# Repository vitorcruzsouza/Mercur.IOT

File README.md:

EN-US: This content was written in both English and Portuguese. To access content in English, [clique here](#enus)

PT-BR: Este conteúdo foi escrito em Inglês e em Português. Para acessar o conteúdo em Português, [clique aqui](#ptbr)

---

# EN/US
# MercurIOT - Sensor Data Transmitter via GSM
readme v1.6

## Contents

<!-- toc -->

- [1. Description](#description)
  - [Objective](#objective)
  - [Behind the name](#behind-the-name)
- [2. Plataform](#platform)
  - [Conceptualization - Electronics](#conceptualization---electronics)
  - [Conceptualization - Code](#conceptualization---code)
  - [Technical Specifications](#technical-specifications)
  - [Bill of Materials](#bill-of-materials)
- [3. Circuit Schematic](#circuit-schematic)
  - [Full System](#full-system)
  - [Power Supply](#power-supply-and-battery-charging)
  - [Microcontroller](#microcontroller)
  - [GSM Communication](#gsm-communication)
  - [Sensor 16-bit ADC](#sensor-16bit-adc)
- [4. Printed Circuit Board (PCB)](#printed-circuit-board-pcb)
  - [2D Visualization of All Layers](#2d-visualization-of-all-layers)
  - [2D Visualization of Top Layer](#2d-visualization-of-top-layer)
  - [2D Visualization of Bottom Layer](#2d-visualization-of-bottom-layer)
- [5. 3D Render of the PCB](#3d-render-of-the-pcb)
  - [Top View](#top-view)
  - [Bottom View](#bottom-view)
  - [Isometric View](#isometric-view)

- [About me](#about-me)

<!-- tocstop -->

## Description

#### Objective
Fully developing a wireless data transmission solution for industrial applications, capable of sending 500kB of sensing data remotely to be used in machine operation conditions monitoring.

The scope of this project encopasses the development of both the PCB and firmware required for operation of the microcontrollers utilized.

#### Behind the name
Inspired by the greek god Mercury, son of Zeus and messenger of the gods, MercurIOT was developed with the purpose of delivering a flexible platform, upon which multiple IOT communication solutions can be created.

## Platform 

### Conceptualization - Electronics:

To send sensor information to a distant receiver, the **GSM tecnology** was selected - the same used for 3G/4G mobile data plans - due to the ease of access to nacional brazillian infrastructure to mobile network systems (where this project was conceived), thus high capacity for long distance tranmissions.

Therefore, the **SIM7600EH** GSM communication chip was chosen, since it presents an easy to use yet powerful list of commands, high market availability and broad documentation.

For controlling the whole system and being responsible for converting the sensor data into commands the SIM7600 can understand, the Atmel **ATMEGA8U2-MU** was selected as a suitable microcontroller. Aside from having very broad documentation and market availability for being one the chips used by Arduino boards, the ATMEGA8 is specially handy for having integrated USB communication, simplifying the final board layout. Its 16MHz clock shall be sufficient to execute all of the communication with no major delays.

One of the limitations of the ATMEGA8, however, is the relatively low resolution of its ADC (Analog to Digital Converter chip), which has a 10 bit resolution (maximum of 1024 individual values in any readings). Therefore, an accompanying **ADS1115** chip was selected to improve the data quality the MercurIOT board can supply. This IC has a 16 bit resolution (max. 65,536 values) for analog readings, it can communicate in I2C protocol with other chips in its network, and can support up to 4 individual analog inputs. For this project, however, we're only going to use one.

Finally, to power the whole system, a **18650 Lithium-Ion** cell was selected, since this type of battery chemistry is very common and is currently one of the best options on Power Density to Price and/or size. Utilizing Li-Ion cells in this project allows it to be recharged, but adds a degree of complexity by requiring some battery monitoring and protection features. For this, the **BQ29707DSET** battery management IC is being used (features include overcharge protection, overdischarge protection, overcurrent protection) in conjunction with the **MT3608** boost-converter for stabilizing a 5VDC supply rail to all other electronics.

### Conceptualization - Code:

To construct a wireless transmission solution, there are a few major things that have to be considered. The first is what information is going to be sent, the second is how it is going to be sent, and third but not least how it is going to be interpreted by what's receiving it.

This way, the first problem that need to be tackled is the **information source** itself. In this project, for demonstration purposes, a hypothetical, unspecified, pre-amplified analog sensor is going to be used, as this is encopasses almost any type of application that telemetry sensors can be used in, since most physical quantity sensing devices output analog (voltage or current) signals.

Since a 16-bit capabe Analog to Digital Converter (ADC) is being used to capture these sensed signals, these 16-bit values have to be processed accordingly. For that, the Adafruit_ADS1015.h library is used, to facilitate I2C communication between the microcontroller and the ADC unit and to interpret the information.

Assuming a server is going to receive sensed data and utilize it, this processed information need to be sent via some medium. For this, the SIM7600EH chip has a list of GSM commands to perform varying tasks. If sent from the microcontroller to the GSM IC via serial UART communication, these commands will each perform an action through the 3G/4G communication line. [Here's a full list of AT commands and instructions on how to use them here.](https://usermanual.wiki/Document/SIM7500SIM760020SeriesAT20Command20ManualV107.443047306/html)

The information that is going to be transmitted, however, needs to be encoded in a certain protocol, so that both parties of this system - client (transmitter) and server (receiver) - can understand what is being relayed; and more critically, know what to do with each information given.

For this, the MQTT (Message Queuing Telemetry Transport) is used. It is a protocol based on TCP/IP network communication that simplifies parallel data transmission between multiple parties, specially for IoT applications such as this one, while providing a light and simple framework for less powerful devices to run on. [Read this for more information on how the MQTT protocol works.](https://randomnerdtutorials.com/what-is-mqtt-and-how-it-works/)

Joining the AT (GSM) and MQTT communication formats, we can compile the data collected by whichever sensor is plugged into the MercurIOT transmitter, and send it to a MQTT topic dedicated to captured sensor data, which then can be subscribed to by any software or BI (Business Inteligence) suite that whishes to utilize or display that information.

### Technical Specifications

#### Electronics

##### Control
- Microcontrolador: ATmega8U2-MU
- IC USB Communication: ATmega8U2-MU
- IC GSM Communication: SIM7600E-H
##### Power supply
- IC Battery Management: BQ29707DSET
- IC Voltage Regulator: MT3608
- Battery: Li-Ion 18650 cell
##### Sensing
- IC 16-bits Analog-Digital Converter: ADS1115

#### Code
- Library Adafruit_ADS1015.h (for I2C communication with the 16bit ADC)
- Library SoftwareSerial.h (for serial UART communication with the GSM and MQTT)
- Libraries Arduino.h, Wire.h e ArduinoLowPower.h (for using the native Arduino platform functionalities)
##### Software
- Development Environment: VSCode
- Platform: Plaform.io

### Bill of Materials

[Link to the Bill of Materials file, complete with links for ordering the parts used globally.](https://github.com/vitorcruzsouza/Mercur.IOT_TRACTIAN/blob/main/docs/BOM.md)

## Circuit Schematic
[Link to folder with circuit and PCB ECAD files.](https://github.com/vitorcruzsouza/Mercur.IOT_TRACTIAN/tree/main/hardware_sch/Mercurio_wirelessTransmitter)

### Full System
[Link to the full schematic file.](https://github.com/vitorcruzsouza/Mercur.IOT_TRACTIAN/blob/main/docs/Mercurio_SCHEMATIC-SHEET.pdf)

### Power Supply and Battery Charging

The circuit above utilizes a BQ2970 battery management IC to monitor the lithium-ion battery's voltage and offer multiple protections. By utilizing a selection of multiple internal comparators, the IC monitors the voltage coming from the positive side of the battery through the "BAT" pin 5. Either when the voltage is too high (±4.2V), too low (±3.4V) or the current is too high (overcurrent or short-circuit), the IC deactivates of its "COUT" or "DOUT" outputs to disconnect the battery's negative side to Ground, through its two CSD16301Q2 MOSFET switches.

Through the use of the MT3608 boost converter IC, both the battery's and the USB port's voltage are steped-up and regulated to 5VDC, for supplying both the ATMEGA and the SIM7600 chips. By using a zener diode between the USB port and the battery, as well as one between the boost converter an all of the componentes supplied, the circuit can be both powered on by the USB port and charge the battery simultaneously without causing a power loop.

### Microcontroller

Together with the microcontroller are a couple of passive components to allow its basic functioning, like a 16MHz clock crystal and accompanying oscillating capacitors, varistors for USB power protection and a ferrite bead for filtering, a 500mA fuse between the power circuit and the VCC port of the ATMEGA chip, a RESET button and 6 open pins (ICSP) for connecting configuration signals, such as boot loading and resetting once again.

### GSM Communication

In this schematic, two S8050 transistors can be observed in series with the TXD and RXD transmission lines that are used to connect the SIM7600E-H and the ATMEGA8U-MU via UART. This is used to decouple both chips while no data is being transmitted, since the very TXD and RXD lines activate the transistors that let the data bits pass, so that these wires do not act as antennas and pickup any interference, stopping any of the two ICs accidentally interpret noise as information.

Pins 17 - 20 are connected to the SIM card slot and therefore the SIM card inserted, and pin 82 is connected to a SMA antenna connector, so that any type or size of antenna desired can be used.

The "PWRKEY" and "RESET" are pulled to ground so that the IC is always active. One improvement this circuit design could benefit from is having the microcontroller, via a switching device, have the option to activate or deactivate both the Reset and Power-Key pins so that the IC can be rebooted or turned off completely for power saving measures.

### Sensor 16bit ADC

Last but not least, the ADS1115 16-bit ADC is connected to the SCL and SCA pins of the ATMEGA microcontroller, through which the ADC relays the sensed analog  signals through I2C serial communication. The sensor, whichever one may be chosen for the application, can be connected to the J4 screw terminal following the "VCC, Signal, GND" pinout standard.

## Printed Circuit Board (PCB)

### 2D Visualization of All Layers

For information all data lines excluding the antenna line, the traces were set to 10 mils (0.254 mm). For all other lines (power lines and antenna), the traces were set to 20 mils (0.5 mm), so that a maximum of 1.5 A can be supplied to all components and used for more power-intensive LTE data transmission.

### 2D Visualization of Top Layer

### 2D Visualization of Bottom Layer

## 3D Render of the PCB

### Top View

### Bottom View

### Isometric View

## About me

### Contact info:
<p>Vitor Cruz Souza<br>
São Paulo, SP, Brazil<br>
E-mail: vitor.cruz.souza.2001@gmail.com</p>

---

[Back to the top.](#contents)

---

# PT/BR
# MercurIOT - Transmissor de Dados de Sensor via GSM
readme v1.52

(Esta sessão ainda não foi totalmente traduzida).

## Conteúdos

<!-- toc -->

- [1. Descrição](#descrição)
  - [Objetivo](#objetivo)
  - [Por trás do nome](#por-trás-do-nome)
- [2. Plataforma](#plataforma)
  - [Conceitualização](#conceitualização)
  - [Especificações Técnicas](#especificações-técnicas)
  - [Lista de Materiais](#lista-de-materiais)
- [3. Esquemático do Circuito](#esquemático-do-circuito)
  - [Sistema Completo](#sistema-completo)
  - [Alimentação e Bateria](#alimentação-e-bateria)
  - [Microcontrolador](#microcontrolador)
  - [Comunicação GSM](#comunicação-gsm)
  - [ADC 16bits do Sensor](#adc-16bits-do-sensor)
- [4. Placa de Circuito Impresso (PCI)](#placa-de-circuito-impresso-pci)
  - [Visualização 2D de Todas as Camadas](#visualização-2d-de-todas-as-camadas)
  - [Visualização 2D da Camada Superior](#visualização-2d-da-camada-superior)
  - [Visualização 2D da Camada Inferior](#visualização-2d-da-camada-inferior)
- [5. Renderização 3D da PCI](#renderização-3d-da-pci)
  - [Vista Superior](#vista-superior)
  - [Vista Inferior](#vista-inferior)
  - [Vista Isométrica](#vista-isométrica)

- [Sobre mim](#sobre-mim)

<!-- tocstop -->

## Descrição

#### Objetivo
O objetivo do projeto MercurIOT é desenvolver uma solução completa de transmissão de dados para aplicações industriais, capaz de enviar 500kB de dados de sensoriamento remotamente, a serem usados no monitoramento de condições de operação de máquinas.

O escopo deste projeto abriga o desenvolvimento de ambos PCI e firmware necessário para operação dos microcontroladores utilizados.

#### Por trás do nome
Inspirado no deus greco-romano Mercúrio, filho de Zeus e mensageiro dos deuses, o MercurIOT foi desenvolvido com o propósito de entregar uma plataforma flexível, sobre a qual múltiplas soluções de comunicação IOT possam ser criadas.

## Plataforma

### Conceitualização

Para realizar o envio de informações do sensor à distância, foi escolhido utilizar de tecnologia GSM, a mesma utilizada para comunicação 3G/4G em telefonia móvel, devido ao fácil acesso à infraestrutura nacional brasileira de redes móveis (onde este projeto foi concebido) e, portanto, alta capacidade de transmissão de dados à longas distâncias.

### Especificações Técnicas

#### Eletrônica

##### Controle
- Microcontrolador: ATmega8U2-MU
- CI Comunicação USB: ATmega8U2-MU
- CI Comunicação GSM: SIM7600E-H
##### Alimentação
- CI Gerenciamento de Baterias: BQ29707DSET
- CI Regulador de Tensão: MT3608
- Bateria: Li-Ion 18650
##### Sensoriamento
- CI Conversor Analógico Digital 16-bits: ADS1115

#### Código
- Biblioteca Adafruit_ADS1015.h (para comunicação I2C com o ADC de 16bits)
- Biblioteca SoftwareSerial.h (para comunicação serial UART com o GSM e MQTT)
- Bibliotecas Arduino.h, Wire.h e ArduinoLowPower.h (para uso de funcionalidades nativas da plataforma Arduino)

##### Software
- Ambiente de Desenvolvimento: VSCode
- Plataforma: Plaform.io

### Lista de Materiais

[Link para a Lista de Materiais contendo também links para compra internacional dos componentes usados.](https://github.com/vitorcruzsouza/Mercur.IOT_TRACTIAN/blob/main/docs/BOM.md)

## Esquemático do Circuito
[Link para pasta com arquivos ECAD do circuito e PCB.](https://github.com/vitorcruzsouza/Mercur.IOT_TRACTIAN/tree/main/hardware_sch/Mercurio_wirelessTransmitter)

### Sistema Completo
[Link para o arquivo do esquemático completo.](https://github.com/vitorcruzsouza/Mercur.IOT_TRACTIAN/blob/main/docs/Mercurio_SCHEMATIC-SHEET.pdf)

### Alimentação e Bateria

### Microcontrolador

### Comunicação GSM

### ADC 16bits do Sensor

## Placa de Circuito Impresso (PCI)
[Link para pasta com arquivos ECAD do circuito e PCB.](https://github.com/vitorcruzsouza/Mercur.IOT_TRACTIAN/tree/main/hardware_sch/Mercurio_wirelessTransmitter)

### Visualização 2D de Todas as Camadas

### Visualização 2D da Camada Superior

### Visualização 2D da Camada Inferior

## Renderização 3D da PCI

### Vista Superior

### Vista Inferior

### Vista Isométrica

## Sobre mim

### Informações de contato:
<p>Vitor Cruz Souza<br>
São Paulo, SP, Brasil<br>
E-mail: vitor.cruz.souza.2001@gmail.com</p>

---

[Ir para o topo.](#conteúdos)

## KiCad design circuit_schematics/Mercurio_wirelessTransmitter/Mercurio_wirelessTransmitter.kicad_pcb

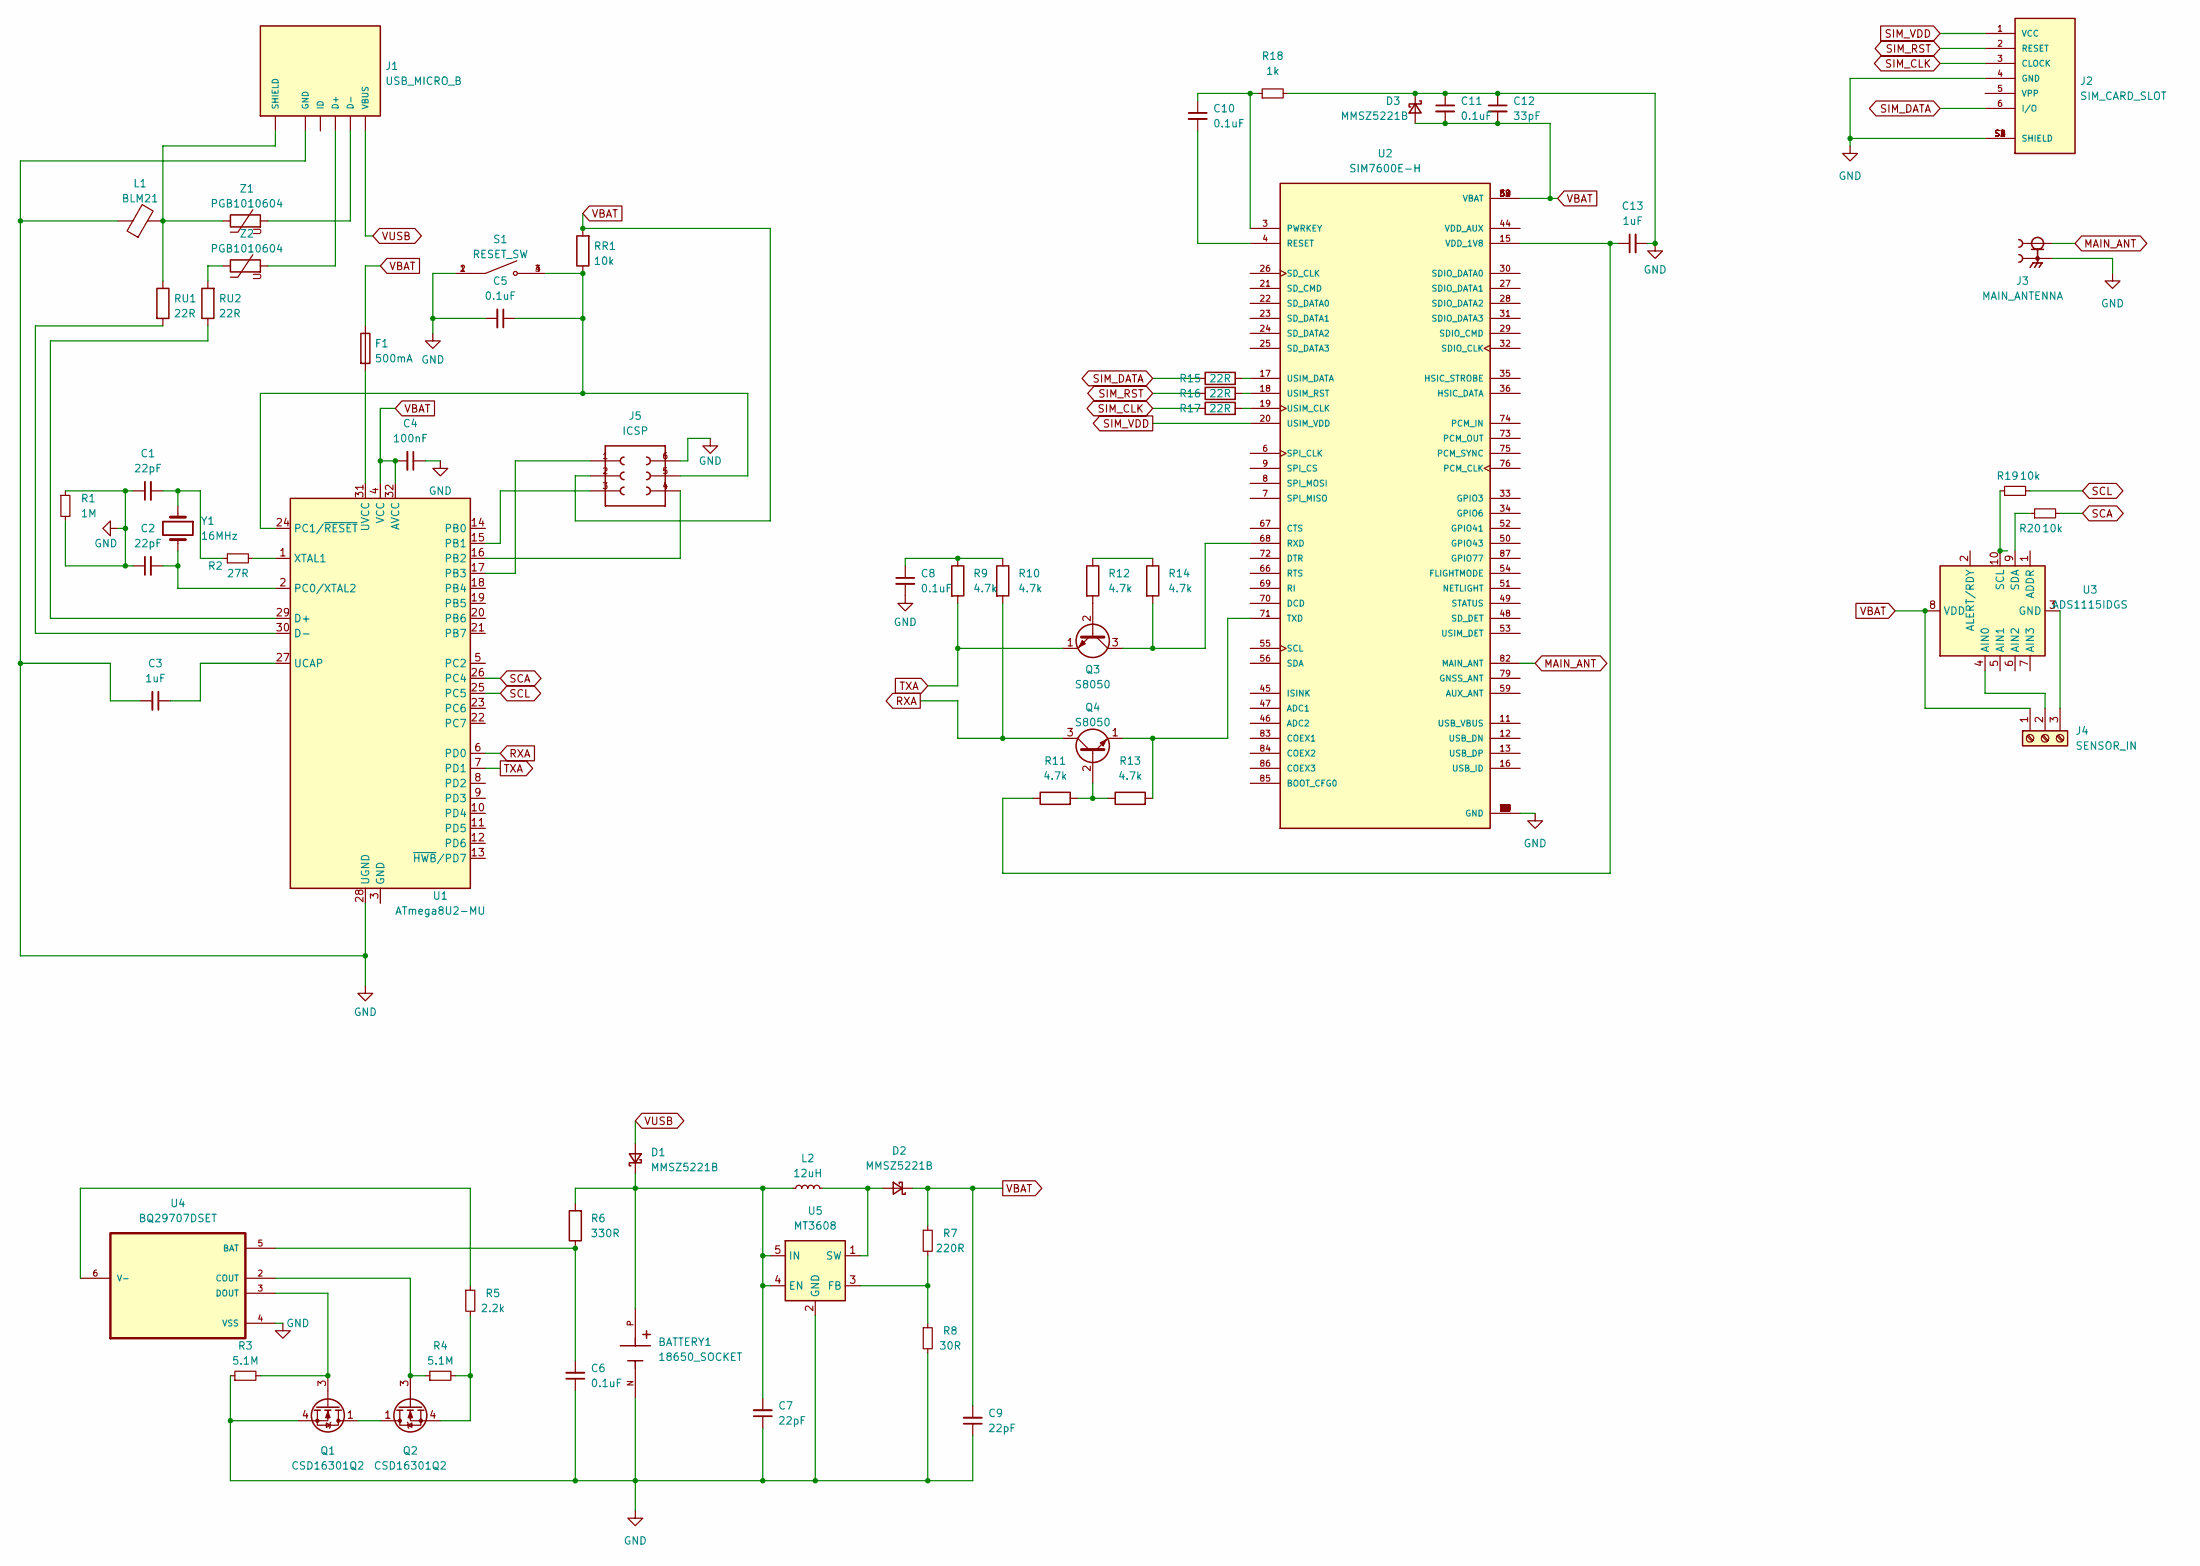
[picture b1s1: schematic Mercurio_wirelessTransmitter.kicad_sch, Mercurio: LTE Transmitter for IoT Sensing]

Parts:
BATTERY1: 18650_SOCKET; BAT_1043; PARTREV H
C1, C2, C7, C9: 22pF; C_0201_0603Metric
C3, C13: 1uF; C_0201_0603Metric
C4: 100nF; C_0201_0603Metric
C5, C6, C8, C10, C11: 0.1uF; C_0201_0603Metric
C12: 33pF; C_0201_0603Metric
D1, D2, D3: MMSZ5221B; D_0201_0603Metric
F1: 500mA; Fuse_0402_1005Metric
J1: USB_MICRO_B; GCT_USB3075-30-A; PARTREV D3
J2: SIM_CARD_SLOT; WURTH_693010020611; PARTREV F
J3: MAIN_ANTENNA; LINX_CONSMA001-SMD-G; PARTREV F
J4: SENSOR_IN; Altech_AK300_1x03_P5.00mm_45-Degree
J5: ICSP; 61000621121
L1: BLM21; L_0201_0603Metric
L2: 12uH; INDC3216X140N
Q1, Q2: CSD16301Q2; Texas_DQK
Q3, Q4: S8050; TO-92_Inline
R1: 1M; R_0201_0603Metric
R2: 27R; R_0201_0603Metric
R3, R4: 5.1M; R_0201_0603Metric
R5: 2.2k; R_0201_0603Metric
R6: 330R; R_0201_0603Metric
R7: 220R; R_0201_0603Metric
R8: 30R; R_0201_0603Metric
R9, R10, R11, R12, R13, R14: 4.7k; R_0201_0603Metric
R15, R16, R17: 22R; R_0201_0603Metric
R18: 1k; R_0201_0603Metric
R19, R20: 10k; R_0201_0603Metric
RR1: 10k; R_0201_0603Metric
RU1, RU2: 22R; R_0201_0603Metric
S1: RESET_SW; SW_5-1437565-0
U1: ATmega8U2-MU; QFN-32-1EP_5x5mm_P0.5mm_EP3.1x3.1mm
U2: SIM7600E-H; IC_SIM7600E-H; PARTREV 1.01
U3: ADS1115IDGS; TSSOP-10_3x3mm_P0.5mm
U4: BQ29707DSET; SON50P150X150X80-6N
U5: MT3608; SOT-23-6
Y1: 16MHz; Crystal_AT310_D3.0mm_L10.0mm_Horizontal
Z1, Z2: PGB1010604; RV_Disc_D7mm_W3.4mm_P5mm

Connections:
GND: BATTERY1.N, C1.1, C2.1, C3.2, C4.1, C5.2, C6.1, C7.1, C8.2, C9.1, C11.1, C12.1, C13.2, D3.1 (K), J1.5 (GND), J2.4 (GND), J2.S1 (SHIELD), J2.S2 (SHIELD), J2.S3 (SHIELD), J2.S4 (SHIELD), J3.S1, J3.S2, J5.6, L1.1, Q1.4 (S), Q1.7 (S), R1.1, R1.2, R3.1, R8.2, R18.2, S1.1, S1.2, U1.28 (UGND), U2.1 (GND), U2.2 (GND), U2.5 (GND), U2.10 (GND), U2.14 (GND), U2.37 (GND), U2.40 (GND), U2.41 (GND), U2.43 (GND), U2.57 (GND), U2.58 (GND), U2.60 (GND), U2.61 (GND), U2.64 (GND), U2.65 (GND), U2.77 (GND), U2.78 (GND), U2.80 (GND), U2.81 (GND), U4.4 (VSS), U5.2 (GND)
MAIN_ANT: J3.1, U2.82 (MAIN_ANT)
unnamed: BATTERY1.P, C7.2, D1.1 (K), L2.1, R6.2, U5.4 (EN), U5.5 (IN)
unnamed: C1.2, R2.1, Y1.1
unnamed: C2.2, U1.2 (PC0/XTAL2), Y1.2
unnamed: C3.1, U1.27 (UCAP)
unnamed: C5.1, J5.5, RR1.1, S1.3, S1.4, U1.24 (PC1/~RESET)
unnamed: C6.2, R6.1, U4.5 (BAT)
unnamed: C8.1, R9.1, R10.1
unnamed: C10.1, R18.1, U2.3 (PWRKEY)
unnamed: C10.2, U2.4 (RESET)
unnamed: C13.1, R11.1, U2.15 (VDD_1V8)
unnamed: D2.2 (A), L2.2, U5.1 (SW)
unnamed: F1.2, U1.31 (UVCC)
unnamed: J4.2, U3.4 (AIN0)
unnamed: J4.3, U3.3 (GND)
unnamed: J5.1, U1.17 (PB3)
unnamed: J5.3, U1.15 (PB1)
unnamed: J5.4, U1.16 (PB2)
unnamed: J1.S1 (SHIELD), J1.S2 (SHIELD), J1.S3 (SHIELD), J1.S4 (SHIELD), J1.S5 (SHIELD), J1.S6 (SHIELD), L1.2, RU1.1, Z1.1
unnamed: Q1.1 (D), Q1.2 (D), Q1.5 (D), Q1.6 (D), Q1.8 (D), Q2.1 (D), Q2.2 (D), Q2.5 (D), Q2.6 (D), Q2.8 (D)
unnamed: Q1.3 (G), R3.2, U4.3 (DOUT)
unnamed: Q2.3 (G), R4.1, U4.2 (COUT)
unnamed: Q2.4 (S), Q2.7 (S), R4.2, R5.2
unnamed: Q3.2 (B), R12.2
unnamed: Q3.3 (C), R14.2, U2.68 (RXD)
unnamed: Q4.1 (E), R13.2, U2.71 (TXD)
unnamed: Q4.2 (B), R11.2, R13.1
unnamed: R2.2, U1.1 (XTAL1)
unnamed: R5.1, U4.6 (V-)
unnamed: R7.2, R8.1, U5.3 (FB)
unnamed: R12.1, R14.1
unnamed: R15.2, U2.17 (USIM_DATA)
unnamed: R16.2, U2.18 (USIM_RST)
unnamed: R17.2, U2.19 (USIM_CLK)
unnamed: R19.1, U3.10 (SCL)
unnamed: R20.1, U3.9 (SDA)
unnamed: RU1.2, U1.30 (D-)
unnamed: RU2.1, U1.29 (D+)
unnamed: RU2.2, Z2.1
unnamed: U1.3 (GND), U1.33 (GND)
unnamed: J1.2 (D-), Z1.2
unnamed: J1.3 (D+), Z2.2
RXA: Q4.3 (C), R10.2, U1.6 (PD0)
SCA: R20.2, U1.26 (PC4)
SCL: R19.2, U1.25 (PC5)
SIM_CLK: J2.3 (CLOCK), R17.1
SIM_DATA: J2.6 (I/O), R15.1
SIM_RST: J2.2 (RESET), R16.1
SIM_VDD: J2.1 (VCC), U2.20 (USIM_VDD)
TXA: Q3.1 (E), R9.2, U1.7 (PD1)
VBAT: C4.2, C9.2, C11.2, C12.2, D2.1 (K), D3.2 (A), F1.1, J4.1, J5.2, R7.1, RR1.2, U1.4 (VCC), U1.32 (AVCC), U2.38 (VBAT), U2.39 (VBAT), U2.62 (VBAT), U2.63 (VBAT), U3.8 (VDD)
VUSB: D1.2 (A), J1.1 (VBUS)

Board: 2 copper layers, 61 parts (1 on the bottom side), 53 nets, no tracks yet.

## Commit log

2022-05-16 Adicionado arquivo teste.txt ao repositorio
2022-05-16 teste.txt apagado e teste2.txt adicionado
2022-05-16 teste2.txt apagado
2022-05-18 Adicionada pasta component_lib contendo as bibliotecas de componentes.
2022-05-19 Adicionado diretorio do projeto KiCAD do Transmissor Sem Fio.
2022-05-20 Revisada biblioteca de componentes.
2022-05-20 Alteracoes ao esquematico.
2022-05-20 Adicionados componentes para a biblioteca e atualizado o esquematico.
2022-05-22 Esquematico atualizado e lib de componentes atualizada
2022-05-22 Atualizado esquematico e atualizadas as libs de componentes
2022-05-22 Atualizado README.md
2022-05-23 Finalizado esquematico, adicionado PDF do esquematico e atualizadas as libs de componentes
2022-05-23 Atualizados labels de componentes e footprints atribuidos.
2022-05-24 Esquematico finalizado, PCB criada e organizada, lib atualizada.
2022-05-24 Finalizada a PCB 2D e 3D, documentado esquematico e vistas de PCB 2D e 3D
2022-05-24 Arquivos Spectra sobressalentes apagados e pasta docs renomeada.
2022-05-24 Criada tabela 'Bill of Materials' vazia
2022-05-25 Pastas renomeadas e codigo criado
2022-05-25 Add codigo de config GSM
2022-05-26 Finished 500kB transmission code.
2022-05-26 Comentarios e correcoes feitos.
2022-05-26 Atualizado README.md
    update_1
2022-05-26 Atualizado README.md
    update_2
2022-05-26 Atualizado README.md
    update_3
2022-05-26 Atualizado README.md
    update_4
2022-05-26 Finalizado BOM.md
2022-05-26 Atualizado README.md
    update_5
2022-05-31 Atualizado README.md
    update_6
